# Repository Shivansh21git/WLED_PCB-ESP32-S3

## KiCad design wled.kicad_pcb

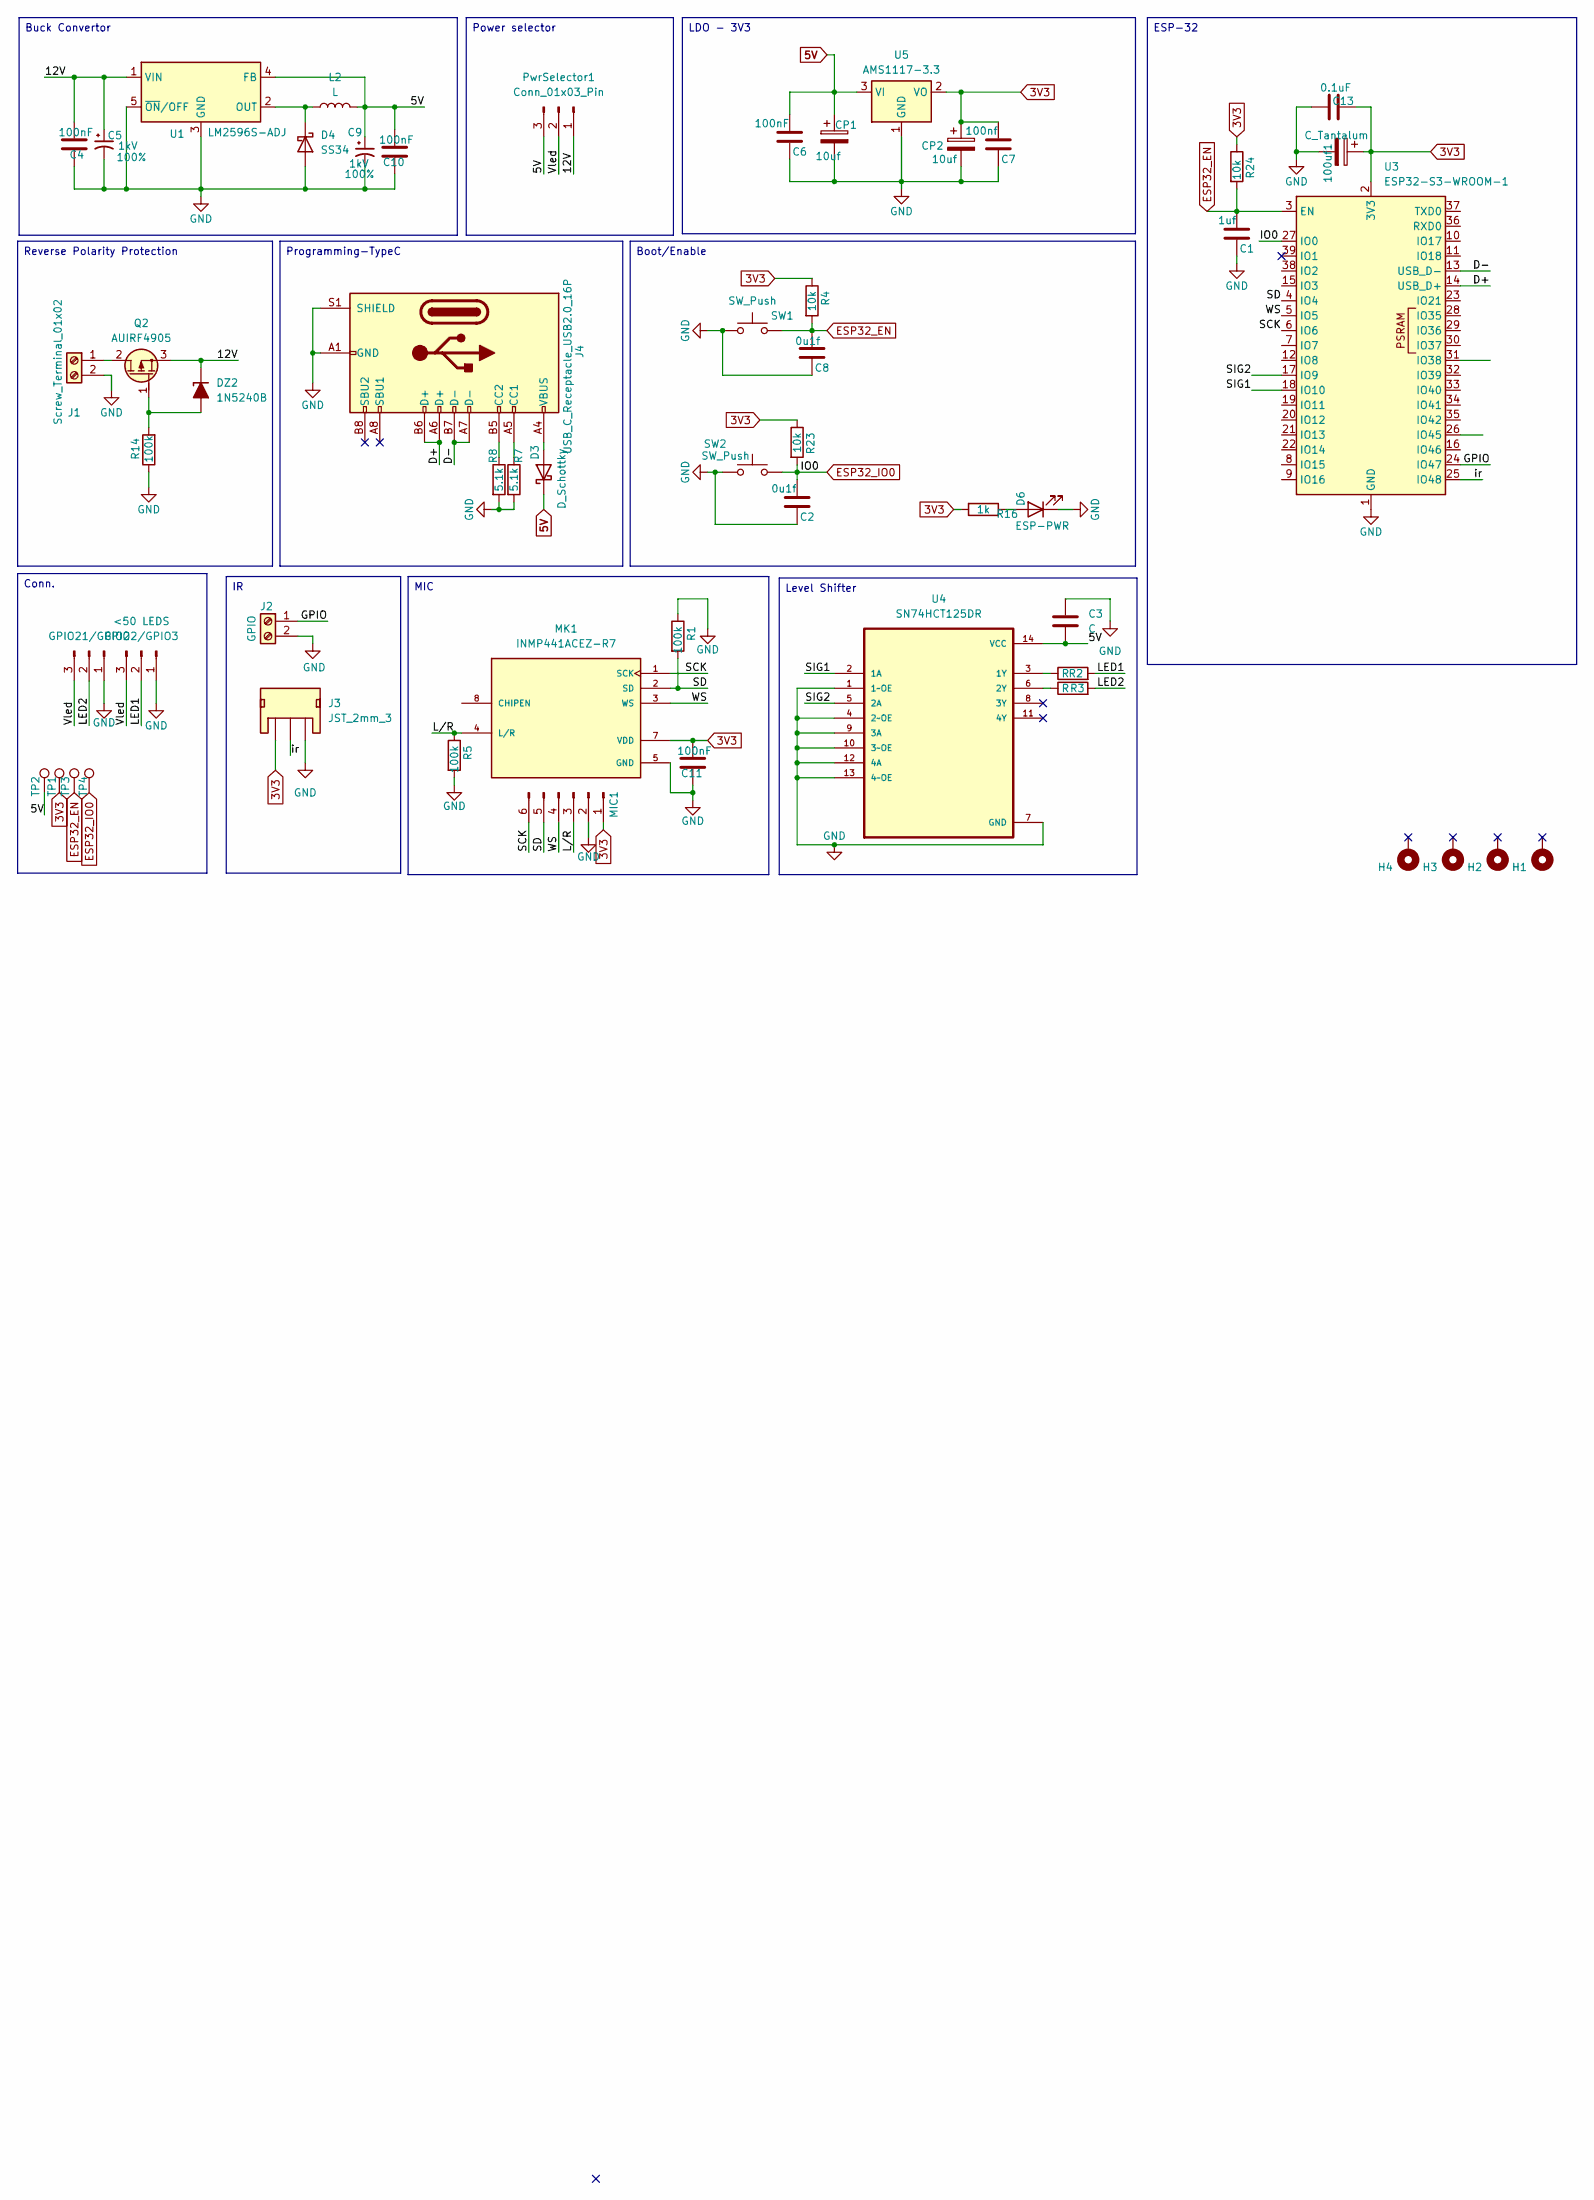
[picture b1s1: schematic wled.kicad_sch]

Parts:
100uf1: C_Tantalum; CP_EIA-3216-10_Kemet-I
C1: 1uf; C_1206_3216Metric_Pad1.33x1.80mm_HandSolder
C2, C8: 0u1f; C_1206_3216Metric_Pad1.33x1.80mm_HandSolder
C3: C; C_1206_3216Metric_Pad1.33x1.80mm_HandSolder
C4, C6, C10, C11: 100nF; C_1206_3216Metric_Pad1.33x1.80mm_HandSolder
C5, C9: C_Polarized_Small; CP_Radial_D8.0mm_P3.50mm; Voltage 1kV; Tolerance 100%
C7: 100nf; C_1206_3216Metric_Pad1.33x1.80mm_HandSolder
C13: 0.1uF; C_1206_3216Metric_Pad1.33x1.80mm_HandSolder
CP1, CP2: 10uf; C_1206_3216Metric_Pad1.33x1.80mm_HandSolder
D3: D_Schottky; R_0805_2012Metric_Pad1.20x1.40mm_HandSolder
D4: SS34; D_SMA
D6: ESP-PWR; C_1206_3216Metric_Pad1.33x1.80mm_HandSolder
DZ2: 1N5240B; D_DO-35_SOD27_P7.62mm_Horizontal_Zener
GPIO2/GPIO3: <50 LEDS; PhoenixContact_MC_1,5_3-G-5.08_1x03_P5.08mm_Horizontal
GPIO21/GPIO2: L1; PhoenixContact_MC_1,5_3-G-5.08_1x03_P5.08mm_Horizontal
H1, H2, H3, H4: MountingHole_Pad; MountingHole_2.5mm_Pad
J1: Screw_Terminal_01x02; PhoenixContact_MC_1,5_2-G-5.08_1x02_P5.08mm_Horizontal
J2: GPIO; TerminalBlock_Xinya_XY308-2.54-2P_1x02_P2.54mm_Horizontal
J3: JST_2mm_3; JST_1x03_P2.0mm_Horizontal_PTH
J4: USB_C_Receptacle_USB2.0_16P; USB_C_Receptacle_GCT_USB4105-xx-A_16P_TopMnt_Horizontal
L2: L; L_10.4x10.4_H4.8
MIC1: Conn_01x06_Pin; JST_EH_B6B-EH-A_1x06_P2.50mm_Vertical
MK1: INMP441ACEZ-R7; MIC_INMP441ACEZ-R7; PARTREV 1.1
PwrSelector1: Conn_01x03_Pin; PinHeader_1x03_P2.54mm_Horizontal
Q2: AUIRF4905; TO-220-3_Horizontal_TabDown_GDS
R1, R5, R14: 100k; R_1206_3216Metric_Pad1.30x1.75mm_HandSolder
R2, R3: R; R_1206_3216Metric_Pad1.30x1.75mm_HandSolder
R4, R23, R24: 10k; R_1206_3216Metric_Pad1.30x1.75mm_HandSolder
R7, R8: 5.1k; R_1206_3216Metric_Pad1.30x1.75mm_HandSolder
R16: 1k; R_1206_3216Metric_Pad1.30x1.75mm_HandSolder
SW1, SW2: SW_Push; SW_PUSH_6mm_H13mm
TP1, TP2, TP3, TP4: TestPoint; TestPoint-1.0mm
U1: LM2596S-ADJ; TO-263-5_TabPin3
U3: ESP32-S3-WROOM-1
U4: SN74HCT125DR; SOIC127P600X175-14N
U5: AMS1117-3.3; SOT-223-3_TabPin2

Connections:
3V3: 100uf1.1, C7.2, C11.2, C13.2, CP2.1, J3.1, MIC1.1, MK1.7 (VDD), R4.1, R16.2, R23.1, R24.1, TP1.1, U3.2 (3V3), U5.2 (VO)
5V: C3.2, C6.2, C9.1, C10.2, CP1.1, D3.1 (K), L2.2, PwrSelector1.3, TP2.1, U1.4 (FB), U4.14 (VCC), U5.3 (VI)
/12V: C4.2, C5.1, DZ2.1 (K), PwrSelector1.1, Q2.3 (S), U1.1 (VIN)
/D+: J4.A6 (D+), J4.B6 (D+), U3.14 (USB_D+)
/D-: J4.A7 (D-), J4.B7 (D-), U3.13 (USB_D-)
/GPIO: J2.1, U3.24 (IO47)
/LED1: GPIO2/GPIO3.2, R2.2
/LED2: GPIO21/GPIO2.2, R3.2
/L/R: MIC1.3, MK1.4 (L/R), R5.1
/SCK: MIC1.6, MK1.1 (SCK), U3.6 (IO6)
/SD: MIC1.5, MK1.2 (SD), R1.2, U3.4 (IO4)
/SIG1: U3.18 (IO10), U4.2 (1A)
/SIG2: U3.17 (IO9), U4.5 (2A)
/Vled: GPIO2/GPIO3.3, GPIO21/GPIO2.3, PwrSelector1.2
/WS: MIC1.4, MK1.3 (WS), U3.5 (IO5)
/ir: J3.2, U3.25 (IO48)
ESP32_EN: C1.2, C8.2, R4.2, R24.2, SW1.2, TP3.1, U3.3 (EN)
ESP32_IO0: C2.2, R23.2, SW2.2, TP4.1, U3.27 (IO0)
GND: 100uf1.2, C1.1, C2.1, C3.1, C4.1, C5.2, C6.1, C7.1, C8.1, C9.2, C10.1, C11.1, C13.1, CP1.2, CP2.2, D4.2 (A), D6.1 (K), GPIO2/GPIO3.1, GPIO21/GPIO2.1, J1.2, J2.2, J3.3, J4.A1 (GND), J4.A12 (GND), J4.B1 (GND), J4.B12 (GND), J4.S1 (SHIELD), MIC1.2, MK1.5 (GND), MK1.6 (GND), MK1.9 (GND), R1.1, R5.2, R7.2, R8.2, R14.1, SW1.1, SW2.1, U1.3 (GND), U1.5 (~ON/OFF), U3.1 (GND), U3.40 (GND), U3.41 (GND), U4.1 (1~OE), U4.4 (2~OE), U4.7 (GND), U4.9 (3A), U4.10 (3~OE), U4.12 (4A), U4.13 (4~OE), U5.1 (GND)
unnamed: D3.2 (A), J4.A4 (VBUS), J4.A9 (VBUS), J4.B4 (VBUS), J4.B9 (VBUS)
unnamed: D4.1 (K), L2.1, U1.2 (OUT)
unnamed: D6.2 (A), R16.1
unnamed: DZ2.2 (A), Q2.1 (G), R14.2
unnamed: J1.1, Q2.2 (D)
unnamed: J4.A5 (CC1), R7.1
unnamed: J4.B5 (CC2), R8.1
unnamed: R2.1, U4.3 (1Y)
unnamed: R3.1, U4.6 (2Y)

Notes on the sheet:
Boot/Enable
Buck Convertor
Reverse Polarity Protection
Conn.
ESP-32
Level Shifter
MIC
Power selector
Programming-TypeC
LDO - 3V3

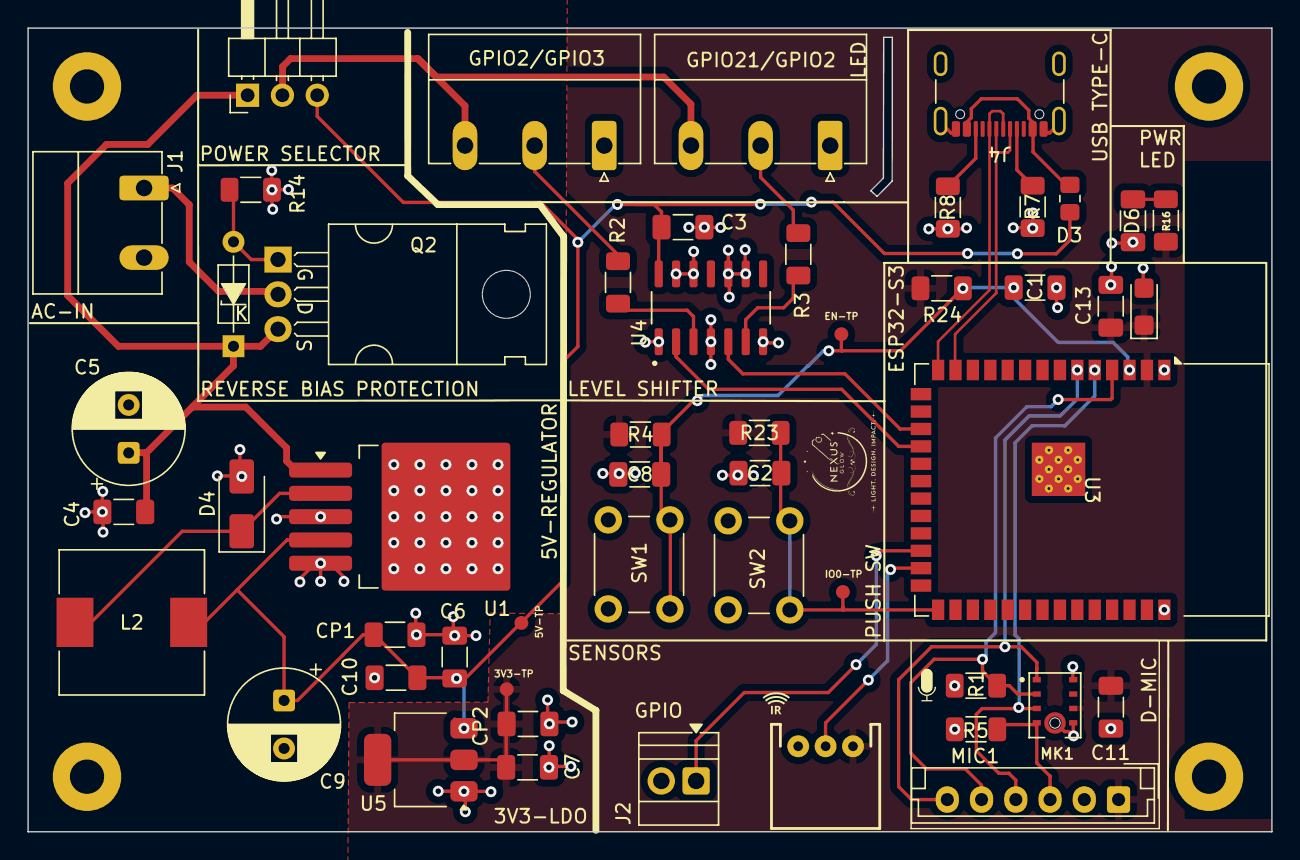
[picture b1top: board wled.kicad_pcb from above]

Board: 2 copper layers, 90.8 x 58.7 mm, 55 parts (0 on the bottom side), 28 nets.

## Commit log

2024-12-09 comit before branch
2025-08-30 soc-update-initial
2026-06-12 version-1.0 rev 2026-04-11
2026-06-29 New wled controller -smd with S3 Wroom-1 chip
2026-06-29 fix-I2S.mic sckPin
